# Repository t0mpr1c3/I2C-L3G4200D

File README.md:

I2C-L3G4200D
============

L3G4200D 3-axis gyroscope breakout board with daisy-chainable I2C header, based on Sparkfun SEN-10612 designed by Jim Lindblom.

Released under the Creative Commons License Attribution-ShareAlike 3.0 http://creativecommons.org/licenses/by-sa/3.0/

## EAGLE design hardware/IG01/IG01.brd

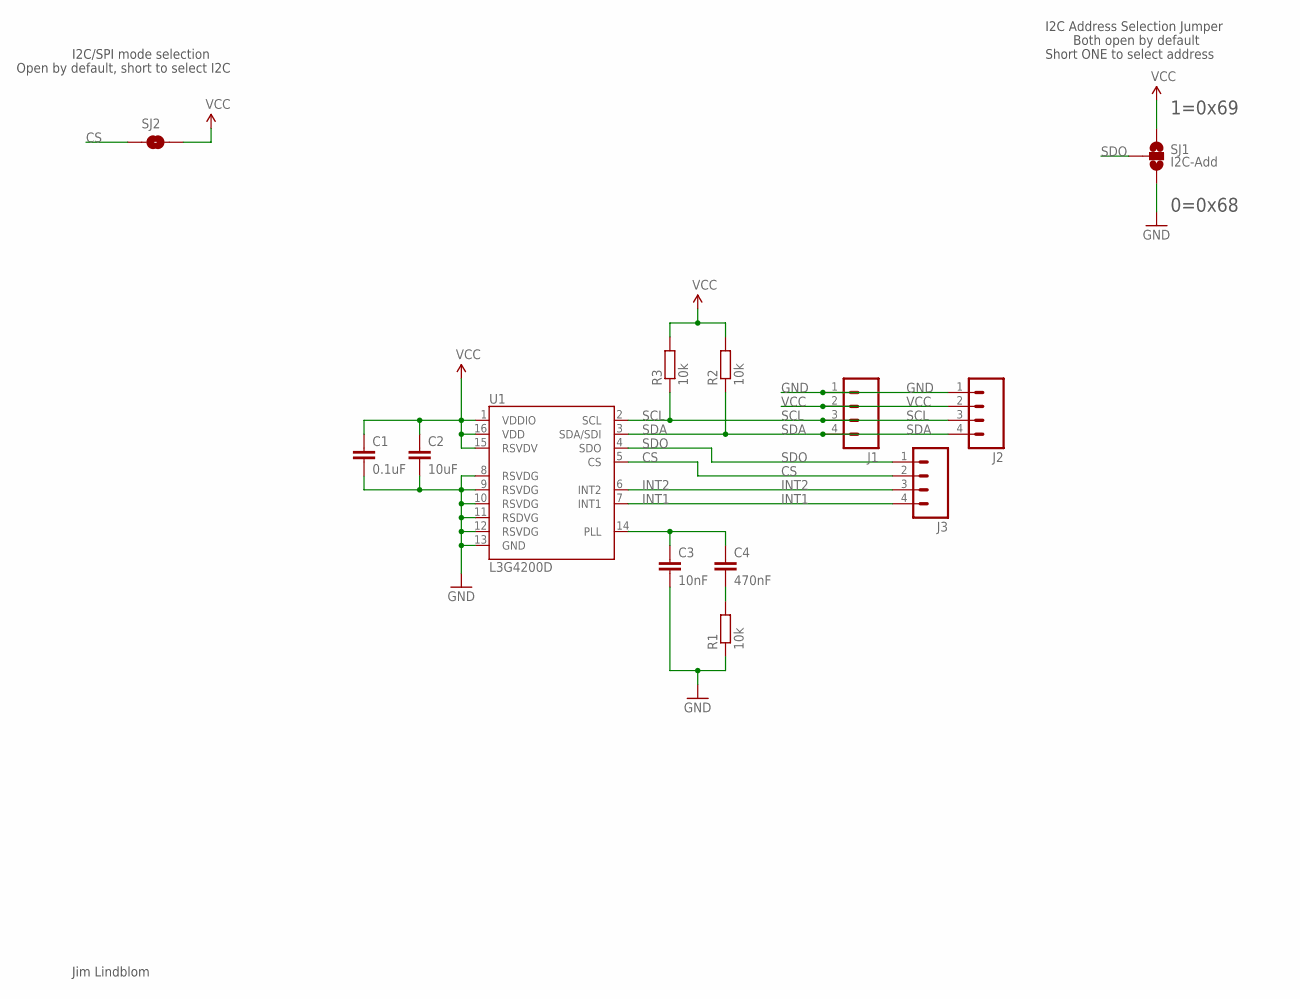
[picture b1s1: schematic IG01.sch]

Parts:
C1: 0.1uF; C0805
C2: 10uF; C1206
C3: 10nF; C0805
C4: 470nF; C0805
J1, J2, J3: M04PTH; 1X04
R1, R2, R3: 10k; M0805
SJ1: I2C-Add; SJ_3
SJ2: I2C-Mode; SJ_2S-NO
U1: L3G4200D; LGA16-4X4

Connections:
CS: J3.2, SJ2.1, U1.5 (CS)
GND: C1.2, C2.2, C3.2, J1.1, J2.1, R1.1, SJ1.3, U1.8 (RSVDG), U1.9 (RSVDG), U1.10 (RSVDG), U1.11 (RSDVG), U1.12 (RSVDG), U1.13 (GND)
INT1: J3.4, U1.7 (INT1)
INT2: J3.3, U1.6 (INT2)
PLL: C3.1, C4.1, U1.14 (PLL)
PLL-2: C4.2, R1.2
SCL: J1.3, J2.3, R3.1, U1.2 (SCL)
SDA: J1.4, J2.4, R2.1, U1.3 (SDA/SDI)
SDO: J3.1, SJ1.2, U1.4 (SDO)
VCC: C1.1, C2.1, J1.2, J2.2, R2.2, R3.2, SJ1.1, SJ2.2, U1.1 (VDDIO), U1.15 (RSVDV), U1.16 (VDD)

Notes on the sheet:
I2C Address Selection Jumper
Jim Lindblom
Both open by default
1=0x69
0=0x68
Short ONE to select address
I2C/SPI mode selection
Open by default, short to select I2C

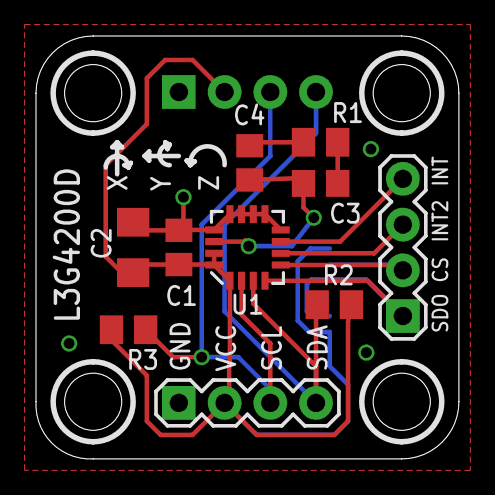
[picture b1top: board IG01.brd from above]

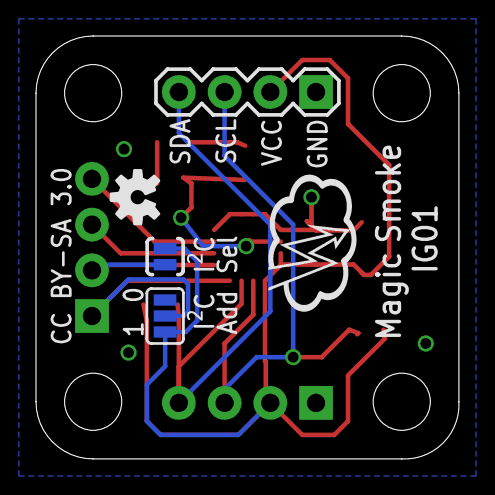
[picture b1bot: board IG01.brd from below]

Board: 4 copper layers, 23.5 x 23.5 mm, 14 parts (4 on the bottom side), 10 nets.

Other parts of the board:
U$3: OSHW-LOGO-S

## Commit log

2013-11-25 GY01 first draft
2013-12-03 gerbers for Seeedstudio
2013-12-03 IG01 final draft

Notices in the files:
hardware/IG01/IG01.brd:
CC BY-SA 3.0
